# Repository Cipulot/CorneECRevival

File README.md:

# CorneECRevival

Revival project of the Corne ECWL.

Left half of Corne EC Revival Rev1.

## **DEPRECATED**

Please be advised that this project has been deprecated, and as of now, it is no longer supported. Regrettably, assistance or help cannot be provided for this deprecated project. The firmware is no longer targeting QMK main, and uses propositions that are now no lonfer working, making the project unusable.

The newer version, Corne EC, will have lots of new feature and will be run as a proper project that you can buy and enjoy right away.

## Introduction

The Corne EC Revival is my personal effort to revive the original Corne ECWL by [sekigon-gonnoc](https://github.com/sekigon-gonnoc).

It boosts full compatibility with the original boards sold by gonnoc while also providing updated QMK support for the latest stable release and a modified set of plates and pcbs, making it compatible with "standard" Corne accessories.

## PCB and Plate

Contrary to the standard Corne, the Corne EC Revival PCBs are not interchangable between left and right half. Plates on the other hand can be used on both sides.

In the [PCB folder](https://github.com/Cipulot/CorneECRevival/blob/main/PCB) there are all the PCB and plate design files. gerber files are in the [Production folder](https://github.com/Cipulot/CorneECRevival/blob/main/Production). The features of each revision are listed in the next section.

The naming scheme reflects the mounting system supported:

- `OG_mounting_[partname]` supports "standard" Corne mounting points
- `[partname]` supports the original Corne ECWL mounting points

Furthermore, to allow for a greater support, both NIZ and Topre housing plates are available for both mounting point configurations.

To see images and further description of the PCB refer to the dedicated section in the Notion build log [here](https://cipulot.notion.site/PCB-Design-9a60de99e9044c61900d82e630ff782b).

## Revisions

### Revision 1 (Rev1)

The Rev1 is the first iteration of the design, 1:1 compatible with the original Corne ECWL from Gonnoc.

The features are therefore shared with the original board with the extension of onboard Trackball and OLED.

Both ECWL mounting system and Standard Corne mounting points are supported with the respective PCB versions.

### Revision 2 (Rev2)

The Rev2 is a departure form the original design approach. It's a 'Ready to go!" board, meaning the MCU and complementary circuit is already onboard.

Added features compared from the Rev1 include:

- Onboard USB-C with ESD protection
- STM32F4x1 MCU for better performance, both cycle wise and in ADC performance compared to 32U4 (also 32U4 prices are to the moon as of now)
- APC (Actuation Point Changer) with predefined actuation points and full scale analog switch control (full board / per key)

Both NIZ and Topre are still supported.

## Production files

Gerber files are provided for all the pcbs of the project. BOM is also available to use. Placement files are WIP.

The prototypes were produced by JLC, therefore pretty much any PCB manufacturer can handle production without any problems.

## Firmware

The firmware folder contains 2 versions of the code based on different QMK releases:

- `EC Revival` based on the latest QMK stable
- `Original ECWL` based on gonnoc's fork, running on an older QMK branch

For the `EC Revival` there are going to be 2 configurations, one for the 32U4 (Rev1) and another for STM32F4x1 (Rev2).

Both have precompiled `*.hex` files based on the code in their respective folders to easily get the board up and running.

## License

<br />This work is licensed under a <a rel="license" href="http://creativecommons.org/licenses/by-nc-sa/4.0/">Creative Commons Attribution-NonCommercial-ShareAlike 4.0 International License</a>.

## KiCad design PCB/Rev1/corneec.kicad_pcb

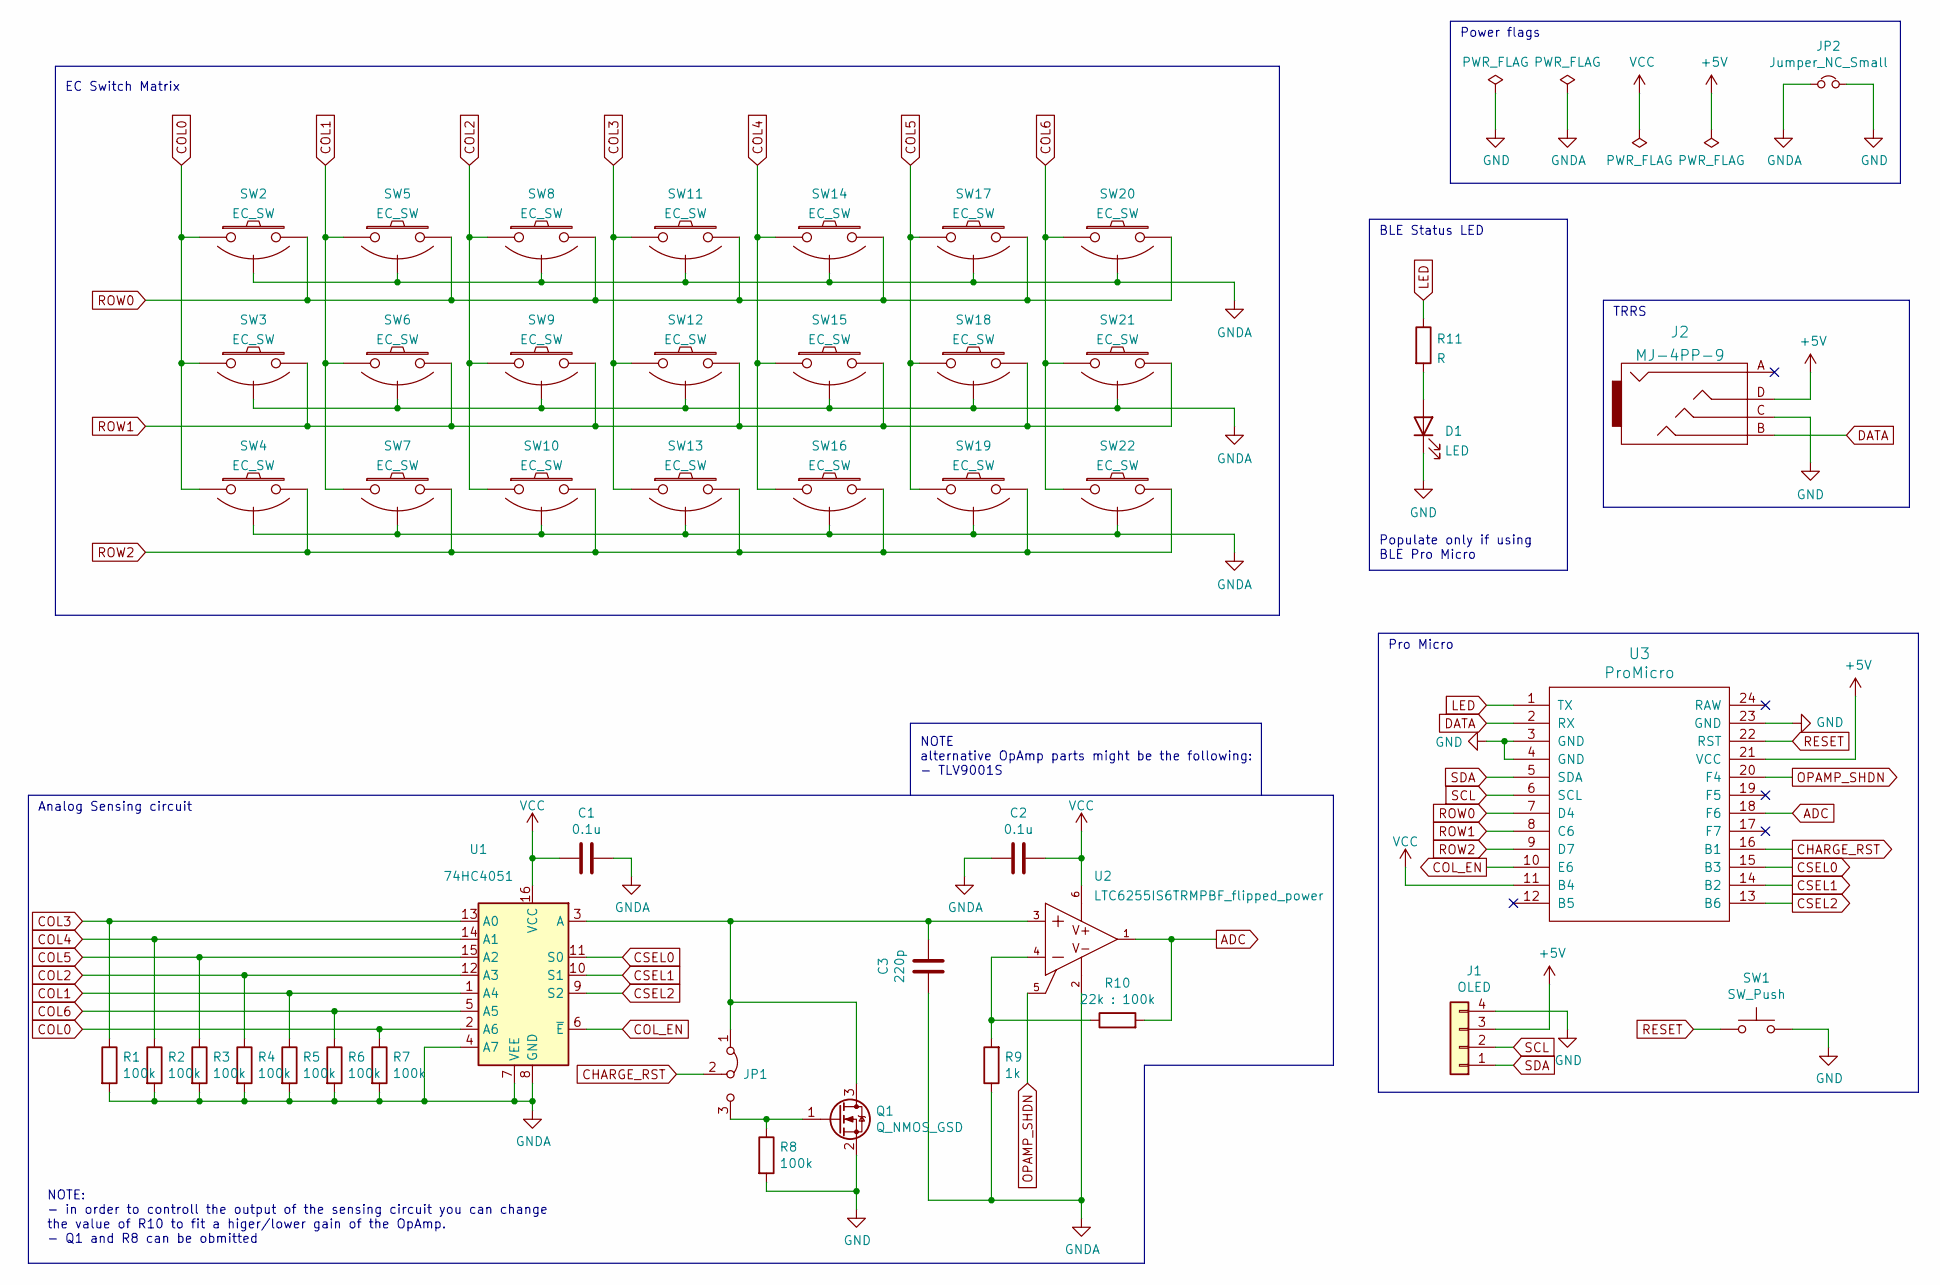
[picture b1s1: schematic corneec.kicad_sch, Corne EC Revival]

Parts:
C1, C2: 0.1u; C_0603_1608Metric_Pad1.08x0.95mm_HandSolder
C3: 220p; C_0603_1608Metric_Pad1.08x0.95mm_HandSolder
D1: LED; D_0603_1608Metric
J1: OLED; OLED_Small
J2: MJ-4PP-9; TRRS-PJ-320A-no-Fmask
JP1: Jumper_3_Bridged12; SolderJumper-3_P1.3mm_Bridged12_Pad1.0x1.5mm
JP2: Jumper_NC_Small; SolderJumper-2_P1.3mm_Bridged_Pad1.0x1.5mm
Q1: Q_NMOS_GSD; SOT-23
R1, R2, R3, R4, R5, R6, R7, R8: 100k; R_0603_1608Metric_Pad0.98x0.95mm_HandSolder
R9: 1k; R_0603_1608Metric_Pad0.98x0.95mm_HandSolder
R10: 22k : 100k; R_0603_1608Metric_Pad0.98x0.95mm_HandSolder
R11: R; R_0603
SW1: SW_Push; SW_3.5x6.0_TH
SW2, SW3, SW4, SW5, SW6, SW7, SW8, SW9, SW10, SW11, SW12, SW13, SW14, SW15, SW16, SW17, SW18, SW19, SW20, SW21, SW22: EC_SW; ecs_pad
U1: 74HC4051; TSSOP16
U2: LTC6255IS6TRMPBF_flipped_power; TSOT-23-6_HandSoldering
U3: ProMicro; Sparkfun_Pro_Micro

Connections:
+5V: J1.3, J2.D, U3.21 (VCC)
ADC: R10.2, U2.1 (OUT), U3.18 (F6)
CHARGE_RST: JP1.2 (C), U3.16 (B1)
COL0: R7.1, SW2.1, SW3.1, SW4.1, U1.2 (A6)
COL1: R5.1, SW5.1, SW6.1, SW7.1, U1.1 (A4)
COL2: R4.1, SW8.1, SW9.1, SW10.1, U1.12 (A3)
COL3: R1.1, SW11.1, SW12.1, SW13.1, U1.13 (A0)
COL4: R2.1, SW14.1, SW15.1, SW16.1, U1.14 (A1)
COL5: R3.1, SW17.1, SW18.1, SW19.1, U1.15 (A2)
COL6: R6.1, SW20.1, SW21.1, SW22.1, U1.5 (A5)
COL_EN: U1.6 (~E), U3.10 (E6)
CSEL0: U1.11 (S0), U3.15 (B3)
CSEL1: U1.10 (S1), U3.14 (B2)
CSEL2: U1.9 (S2), U3.13 (B6)
DATA: J2.B, U3.2 (RX)
GND: D1.1 (K), J1.4, J2.C, JP2.2, Q1.2 (S), R8.2, SW1.2, U3.3 (GND), U3.4 (GND), U3.23 (GND)
GNDA: C1.1, C2.2, C3.2, JP2.1, R1.2, R2.2, R3.2, R4.2, R5.2, R6.2, R7.2, R9.1, SW2.3 (SG), SW3.3 (SG), SW4.3 (SG), SW5.3 (SG), SW6.3 (SG), SW7.3 (SG), SW8.3 (SG), SW9.3 (SG), SW10.3 (SG), SW11.3 (SG), SW12.3 (SG), SW13.3 (SG), SW14.3 (SG), SW15.3 (SG), SW16.3 (SG), SW17.3 (SG), SW18.3 (SG), SW19.3 (SG), SW20.3 (SG), SW21.3 (SG), SW22.3 (SG), U1.4 (A7), U1.7 (VEE), U1.8 (GND), U2.2 (V-)
LED: R11.1, U3.1 (TX)
unnamed: C3.1, JP1.1 (A), Q1.3 (D), U1.3 (A), U2.3 (+IN)
unnamed: D1.2 (A), R11.2
unnamed: JP1.3 (B), Q1.1 (G), R8.1
unnamed: R9.2, R10.1, U2.4 (-IN)
OPAMP_SHDN: U2.5 (~SHDN), U3.20 (F4)
RESET: SW1.1, U3.22 (RST)
ROW0: SW2.2, SW5.2, SW8.2, SW11.2, SW14.2, SW17.2, SW20.2, U3.7 (D4)
ROW1: SW3.2, SW6.2, SW9.2, SW12.2, SW15.2, SW18.2, SW21.2, U3.8 (C6)
ROW2: SW4.2, SW7.2, SW10.2, SW13.2, SW16.2, SW19.2, SW22.2, U3.9 (D7)
SCL: J1.2, U3.6 (SCL)
SDA: J1.1, U3.5 (SDA)
VCC: C1.2, C2.1, U1.16 (VCC), U2.6 (V+), U3.11 (B4)

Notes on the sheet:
TRRS
NOTE alternative OpAmp parts might be the following: - TLV9001S
Populate only if using BLE Pro Micro
Pro Micro
NOTE: - in order to controll the output of the sensing circuit you can change the value of R10 to fit a higer/lower gain of the OpAmp. - Q1 and R8 can be obmitted
EC Switch Matrix
Analog Sensing circuit
BLE Status LED
Power flags

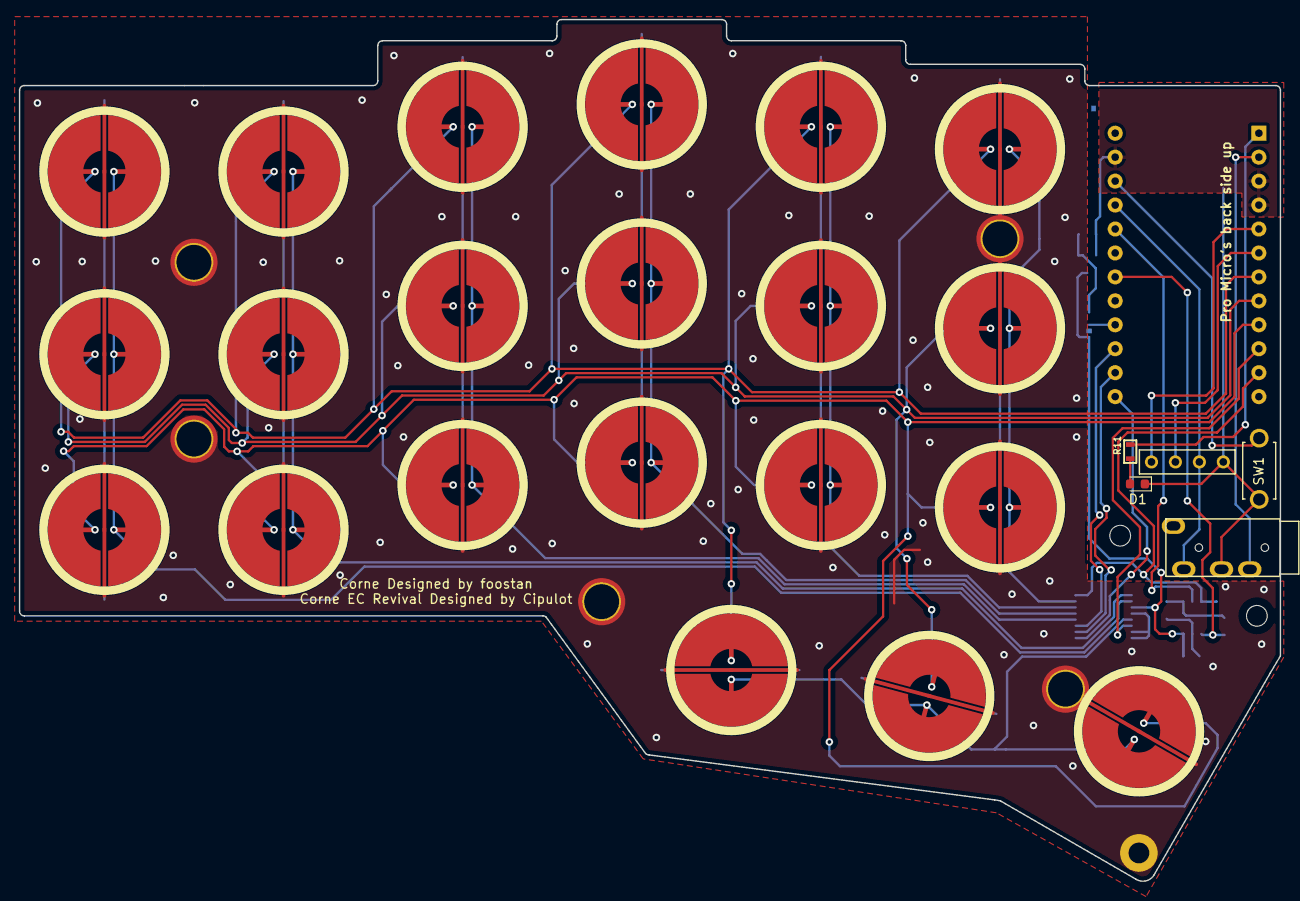
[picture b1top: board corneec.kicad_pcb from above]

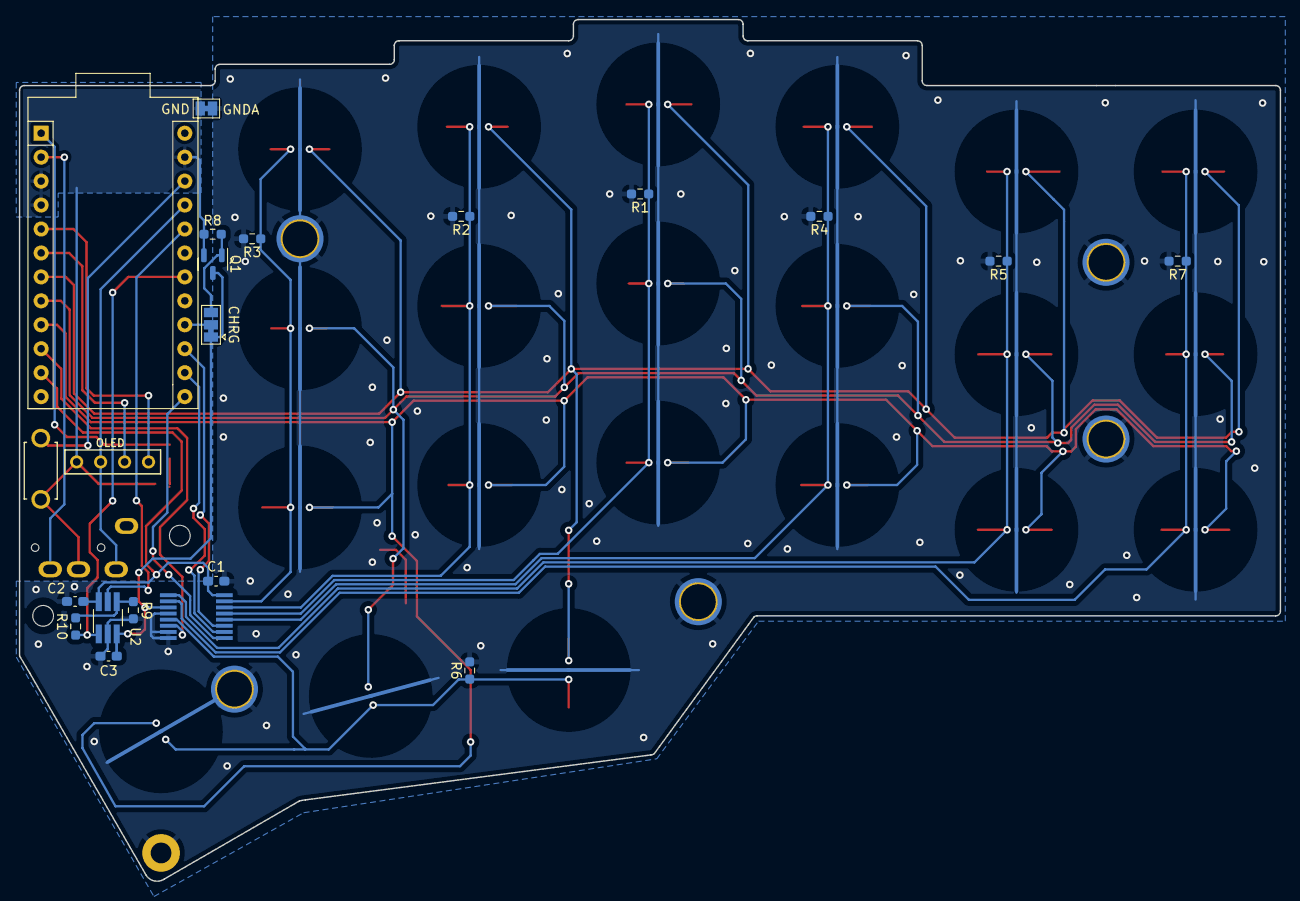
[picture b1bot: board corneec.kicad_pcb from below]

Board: 2 copper layers, 133.8 x 91.4 mm, 46 parts (19 on the bottom side), 30 nets.

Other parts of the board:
H22: MountingHole; HOLE_M2

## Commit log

2023-11-15 Update LICENSE
    Change of License
2024-03-03 Update
    Updated the License for the project and relative details.
2024-06-05 CorneECRevival cleanup

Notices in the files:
PCB/Rev1/corneec.kicad_pcb:
Copyright © 2024 Cipulot
CC-BY-NC-SA-4.0
